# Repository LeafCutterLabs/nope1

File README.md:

# nope1
OP-1/LMN-3 interface based on the RP2040.<br>

Current QMK firmware is very basic (only midi keyboard implemented 53-76 and the LMN-3 CC signals, encoder are now working in vial! analog is not working)<br>
Joystick Analog pins: 26, 27<br>
Known Issues:<br>
	-Joystick switch trace is not connected<br>
 ToDo:<br>
 	-Get Vial running - DONE

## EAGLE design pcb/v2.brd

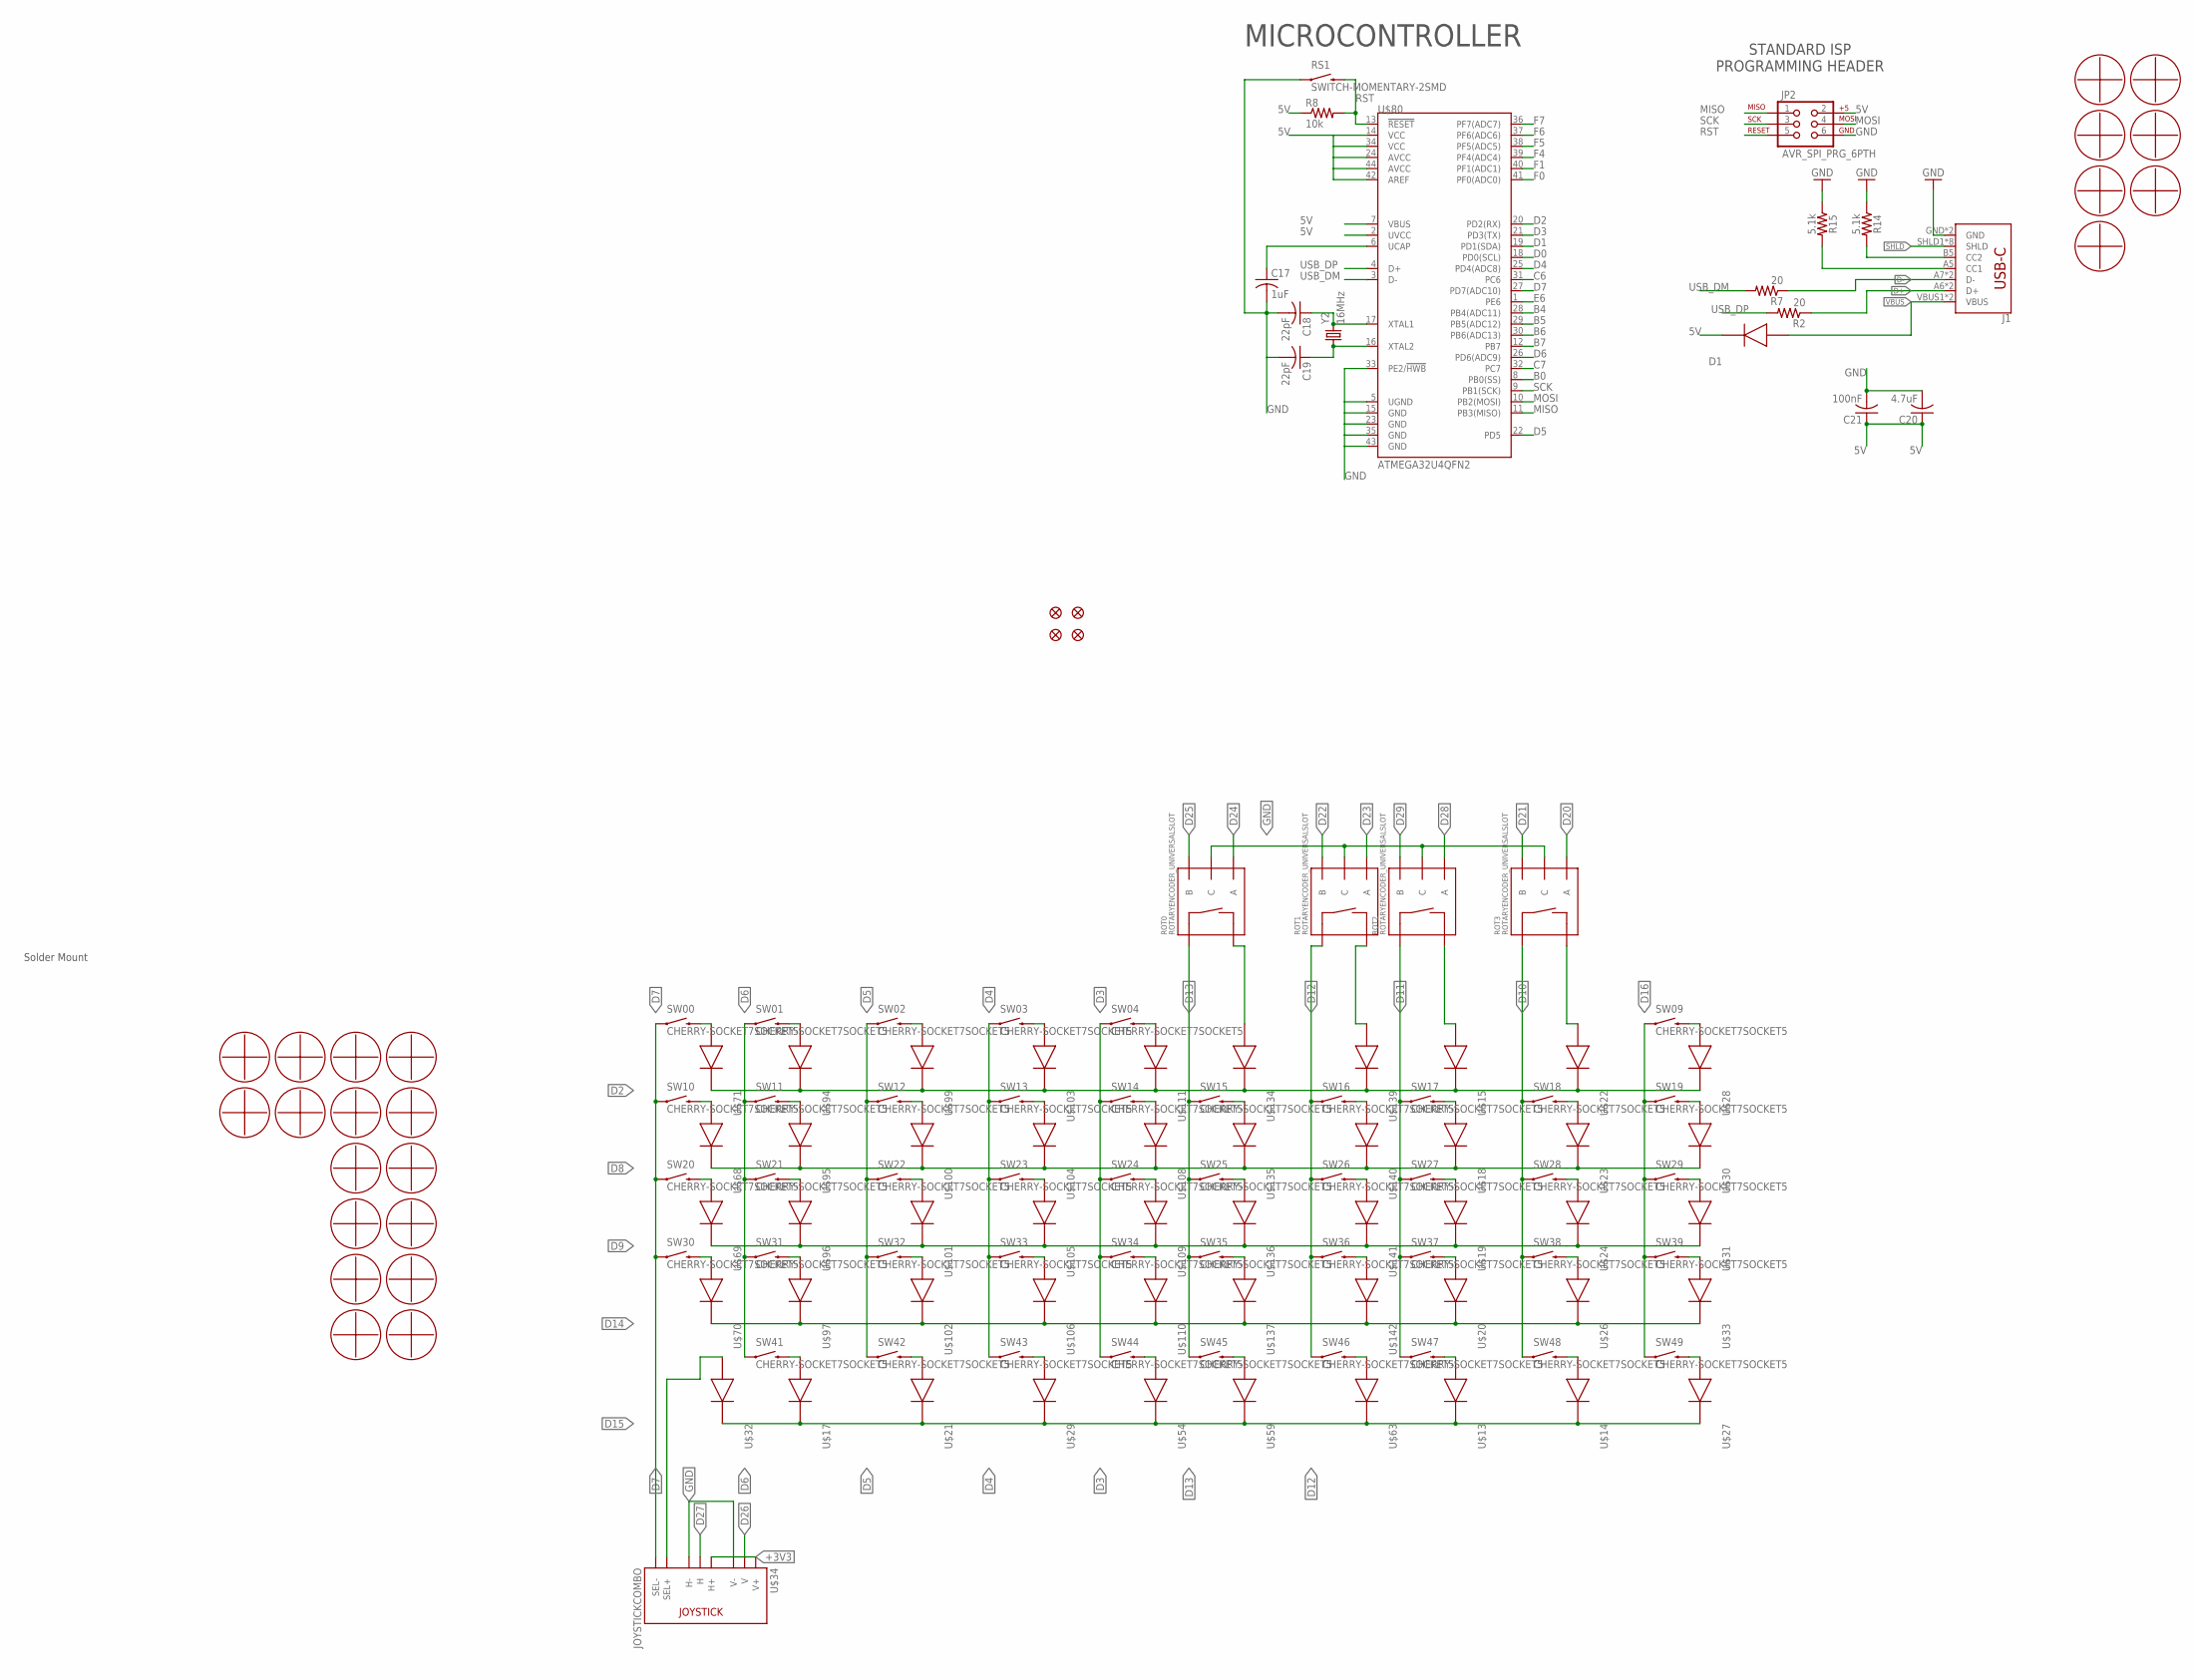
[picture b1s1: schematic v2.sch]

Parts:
C17: 1uF; C0603
C18, C19: 22pF; C0603
C20: 4.7uF; C0603
C21: 100nF; C0603
D1: SCHOTTKY; SOD-123
J1: USB_C16PIN; USB-C-16P
JP2: AVR_SPI_PRG_6PTH; 2X3
R2, R7: 20; R0603
R8: 10k; R0603
R14, R15: 5.1k; 0603
ROT0, ROT1, ROT2, ROT3: ROTARYENCODER_UNIVERSALSLOT; ROTARY_ENC_SLOT
RS1: SWITCH-MOMENTARY-2SMD; TACTILE_SWITCH_SMD
SW00, SW01, SW02, SW03, SW04, SW09, SW10, SW11, SW12, SW13, SW14, SW15, SW16, SW17, SW18, SW19, SW20, SW21, SW22, SW23, SW24, SW25, SW26, SW27, SW28, SW29, SW30, SW31, SW32, SW33, SW34, SW35, SW36, SW37, SW38, SW39, SW41, SW42, SW43, SW44, SW45, SW46, SW47, SW48, SW49: CHERRY-SOCKET7SOCKET5; CHERRY-SOCKET5
U$1, U$2, U$3, U$4, U$5, U$6, U$7, U$8, U$9, U$10, U$11, U$12, U$16, U$25, U$44, U$45: M2MOUNT
U$13, U$14, U$15, U$17, U$18, U$19, U$20, U$21, U$22, U$23, U$24, U$26, U$27, U$28, U$29, U$30, U$31, U$32, U$33, U$54, U$59, U$63, U$68, U$69, U$70, U$71, U$94, U$95, U$96, U$97, U$99, U$100, U$101, U$102, U$103, U$104, U$105, U$106, U$108, U$109, U$110, U$111, U$134, U$135, U$136, U$137, U$139, U$140, U$141, U$142: 1N4148WS; SOD-323SLIM
U$34: JOYSTICKCOMBO
U$35, U$36, U$37, U$40, U$41, U$42, U$43: M2MOUNT3.65HOLE; M2SOLDERC2916348
U$38, U$39, U$62, U$64: FIDUCIAL_1MM
U$80: ATMEGA32U4QFN2; QFN-44-NOPAD
Y2: 16MHz; RESONATOR3225

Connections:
5V: C20.1, C21.1, D1.CAT, JP2.2, R8.1, U$80.2 (UVCC), U$80.7 (VBUS), U$80.14 (VCC), U$80.24 (AVCC), U$80.34 (VCC), U$80.42 (AREF), U$80.44 (AVCC)
+3V3: U$34.H1 (H+), U$34.HS1 (H+), U$34.V1 (V+), U$34.VS1 (V+)
B0: U$80.8 (PB0(SS))
B4: U$80.28 (PB4(ADC11))
B5: U$80.29 (PB5(ADC12))
B6: U$80.30 (PB6(ADC13))
B7: U$80.12 (PB7)
C6: U$80.31 (PC6)
C7: U$80.32 (PC7)
CC3: J1.A5 (CC1), R15.2
CC4: J1.B5 (CC2), R14.2
D0: U$80.18 (PD0(SCL))
D1: U$80.19 (PD1(SDA))
D2: U$15.GND (CAT), U$22.GND (CAT), U$28.GND (CAT), U$71.GND (CAT), U$80.20 (PD2(RX)), U$94.GND (CAT), U$99.GND (CAT), U$103.GND (CAT), U$111.GND (CAT), U$134.GND (CAT), U$139.GND (CAT)
D3: SW04.A (1), SW14.A (1), SW24.A (1), SW34.A (1), SW44.A (1), U$80.21 (PD3(TX))
D4: SW03.A (1), SW13.A (1), SW23.A (1), SW33.A (1), SW43.A (1), U$80.25 (PD4(ADC8))
D5: SW02.A (1), SW12.A (1), SW22.A (1), SW32.A (1), SW42.A (1), U$80.22 (PD5)
D6: SW01.A (1), SW11.A (1), SW21.A (1), SW31.A (1), SW41.A (1), U$80.26 (PD6(ADC9))
D7: SW00.A (1), SW10.A (1), SW20.A (1), SW30.A (1), U$34.B1B (SEL-), U$34.B1B1 (SEL-), U$34.B2B (SEL-), U$34.B2B1 (SEL-), U$80.27 (PD7(ADC10))
D8: U$18.GND (CAT), U$23.GND (CAT), U$30.GND (CAT), U$68.GND (CAT), U$95.GND (CAT), U$100.GND (CAT), U$104.GND (CAT), U$108.GND (CAT), U$135.GND (CAT), U$140.GND (CAT)
D9: U$19.GND (CAT), U$24.GND (CAT), U$31.GND (CAT), U$69.GND (CAT), U$96.GND (CAT), U$101.GND (CAT), U$105.GND (CAT), U$109.GND (CAT), U$136.GND (CAT), U$141.GND (CAT)
D10: ROT3.SW+, SW18.A (1), SW28.A (1), SW38.A (1), SW48.A (1)
D11: ROT2.SW+, SW17.A (1), SW27.A (1), SW37.A (1), SW47.A (1)
D12: ROT1.SW+, SW16.A (1), SW26.A (1), SW36.A (1), SW46.A (1)
D13: ROT0.SW+, SW15.A (1), SW25.A (1), SW35.A (1), SW45.A (1)
D14: U$20.GND (CAT), U$26.GND (CAT), U$33.GND (CAT), U$70.GND (CAT), U$97.GND (CAT), U$102.GND (CAT), U$106.GND (CAT), U$110.GND (CAT), U$137.GND (CAT), U$142.GND (CAT)
D15: U$13.GND (CAT), U$14.GND (CAT), U$17.GND (CAT), U$21.GND (CAT), U$27.GND (CAT), U$29.GND (CAT), U$32.GND (CAT), U$54.GND (CAT), U$59.GND (CAT), U$63.GND (CAT)
D16: SW09.A (1), SW19.A (1), SW29.A (1), SW39.A (1), SW49.A (1)
D20: ROT3.A
D21: ROT3.B
D22: ROT1.B
D23: ROT1.A
D24: ROT0.A
D25: ROT0.B
D26: U$34.V2 (V), U$34.VS2 (V)
D27: U$34.H2 (H), U$34.HS2 (H)
D28: ROT2.A
D29: ROT2.B
D+: J1.A6 (D+), J1.B6 (D+), R2.1
D-: J1.A7 (D-), J1.B7 (D-), R7.1
E6: U$80.1 (PE6)
F0: U$80.41 (PF0(ADC0))
F1: U$80.40 (PF1(ADC1))
F4: U$80.39 (PF4(ADC4))
F5: U$80.38 (PF5(ADC5))
F6: U$80.37 (PF6(ADC6))
F7: U$80.36 (PF7(ADC7))
GND: C17.2, C18.2, C19.2, C20.2, C21.2, J1.GND, J1.GND2 (GND), JP2.6, R14.1, R15.1, ROT0.C, ROT1.C, ROT2.C, ROT3.C, RS1.1, U$34.H3 (H-), U$34.HS3 (H-), U$34.V3 (V-), U$34.VS3 (V-), U$80.5 (UGND), U$80.15 (GND), U$80.23 (GND), U$80.33 (PE2/!HWB), U$80.35 (GND), U$80.43 (GND)
MISO: JP2.1, U$80.11 (PB3(MISO))
MOSI: JP2.4, U$80.10 (PB2(MOSI))
unnamed: U$32.SIGNAL (ANO), U$34.B1A (SEL+), U$34.B1A1 (SEL+), U$34.B2A (SEL+), U$34.B2A1 (SEL+)
unnamed: SW47.B (2), U$13.SIGNAL (ANO)
unnamed: SW48.B (2), U$14.SIGNAL (ANO)
unnamed: ROT2.SW-, U$15.SIGNAL (ANO)
unnamed: SW17.B (2), U$18.SIGNAL (ANO)
unnamed: SW27.B (2), U$19.SIGNAL (ANO)
unnamed: SW37.B (2), U$20.SIGNAL (ANO)
unnamed: SW41.B (2), U$17.SIGNAL (ANO)
unnamed: ROT3.SW-, U$22.SIGNAL (ANO)
unnamed: SW18.B (2), U$23.SIGNAL (ANO)
unnamed: SW28.B (2), U$24.SIGNAL (ANO)
unnamed: SW38.B (2), U$26.SIGNAL (ANO)
unnamed: SW49.B (2), U$27.SIGNAL (ANO)
unnamed: SW09.B (2), U$28.SIGNAL (ANO)
unnamed: SW42.B (2), U$21.SIGNAL (ANO)
unnamed: SW19.B (2), U$30.SIGNAL (ANO)
unnamed: SW29.B (2), U$31.SIGNAL (ANO)
unnamed: SW39.B (2), U$33.SIGNAL (ANO)
unnamed: SW00.B (2), U$71.SIGNAL (ANO)
unnamed: SW43.B (2), U$29.SIGNAL (ANO)
unnamed: SW44.B (2), U$54.SIGNAL (ANO)
unnamed: C17.1, U$80.6 (UCAP)
unnamed: SW45.B (2), U$59.SIGNAL (ANO)
unnamed: SW10.B (2), U$68.SIGNAL (ANO)
unnamed: SW20.B (2), U$69.SIGNAL (ANO)
unnamed: SW30.B (2), U$70.SIGNAL (ANO)
unnamed: SW46.B (2), U$63.SIGNAL (ANO)
unnamed: SW01.B (2), U$94.SIGNAL (ANO)
unnamed: SW11.B (2), U$95.SIGNAL (ANO)
unnamed: SW21.B (2), U$96.SIGNAL (ANO)
unnamed: SW31.B (2), U$97.SIGNAL (ANO)
unnamed: SW02.B (2), U$99.SIGNAL (ANO)
unnamed: SW12.B (2), U$100.SIGNAL (ANO)
unnamed: SW22.B (2), U$101.SIGNAL (ANO)
unnamed: SW32.B (2), U$102.SIGNAL (ANO)
unnamed: SW14.B (2), U$108.SIGNAL (ANO)
unnamed: SW24.B (2), U$109.SIGNAL (ANO)
unnamed: SW34.B (2), U$110.SIGNAL (ANO)
unnamed: SW03.B (2), U$103.SIGNAL (ANO)
unnamed: SW13.B (2), U$104.SIGNAL (ANO)
unnamed: SW23.B (2), U$105.SIGNAL (ANO)
unnamed: SW33.B (2), U$106.SIGNAL (ANO)
unnamed: SW04.B (2), U$111.SIGNAL (ANO)
unnamed: ROT0.SW-, U$134.SIGNAL (ANO)
unnamed: SW15.B (2), U$135.SIGNAL (ANO)
unnamed: SW25.B (2), U$136.SIGNAL (ANO)
unnamed: SW35.B (2), U$137.SIGNAL (ANO)
unnamed: ROT1.SW-, U$139.SIGNAL (ANO)
unnamed: SW16.B (2), U$140.SIGNAL (ANO)
unnamed: SW26.B (2), U$141.SIGNAL (ANO)
unnamed: SW36.B (2), U$142.SIGNAL (ANO)
RST: JP2.5, R8.2, RS1.3 (2), U$80.13 (!RESET)
SCK: JP2.3, U$80.9 (PB1(SCK))
SHLD: J1.SHLD1 (SHLD), J1.SHLD2 (SHLD), J1.SHLD3 (SHLD), J1.SHLD4 (SHLD), J1.SHLD5 (SHLD), J1.SHLD6 (SHLD), J1.SHLD7 (SHLD), J1.SHLD8 (SHLD)
USB_DM: R7.2, U$80.3 (D-)
USB_DP: R2.2, U$80.4 (D+)
VBUS: D1.ANO, J1.VBUS1 (VBUS), J1.VBUS2 (VBUS)
XTAL1: C18.1, U$80.17 (XTAL1), Y2.P3 (2)
XTAL2: C19.1, U$80.16 (XTAL2), Y2.P1 (1)

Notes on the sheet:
Solder Mount
MICROCONTROLLER
STANDARD ISP PROGRAMMING HEADER

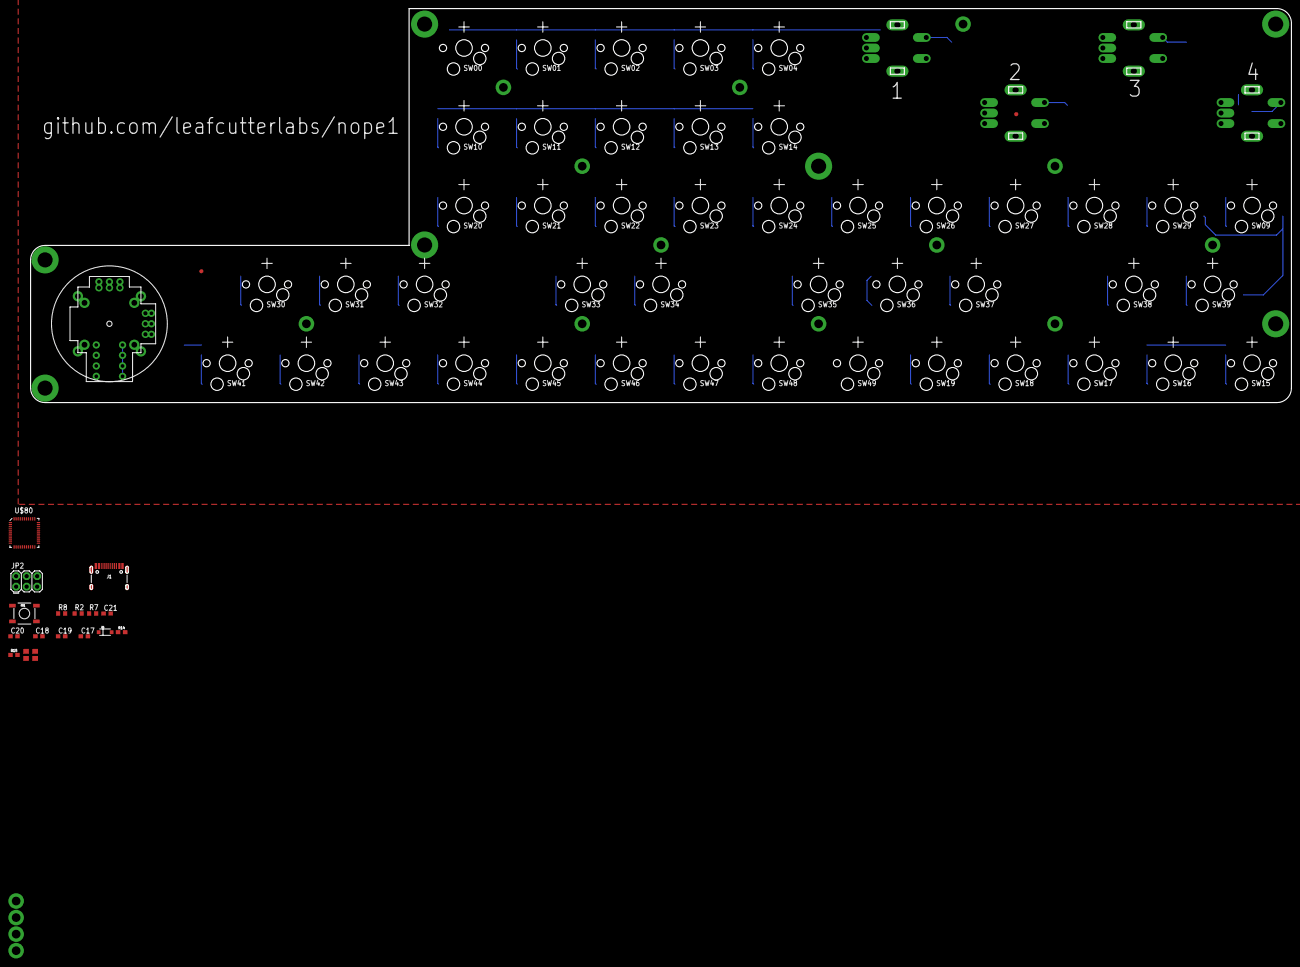
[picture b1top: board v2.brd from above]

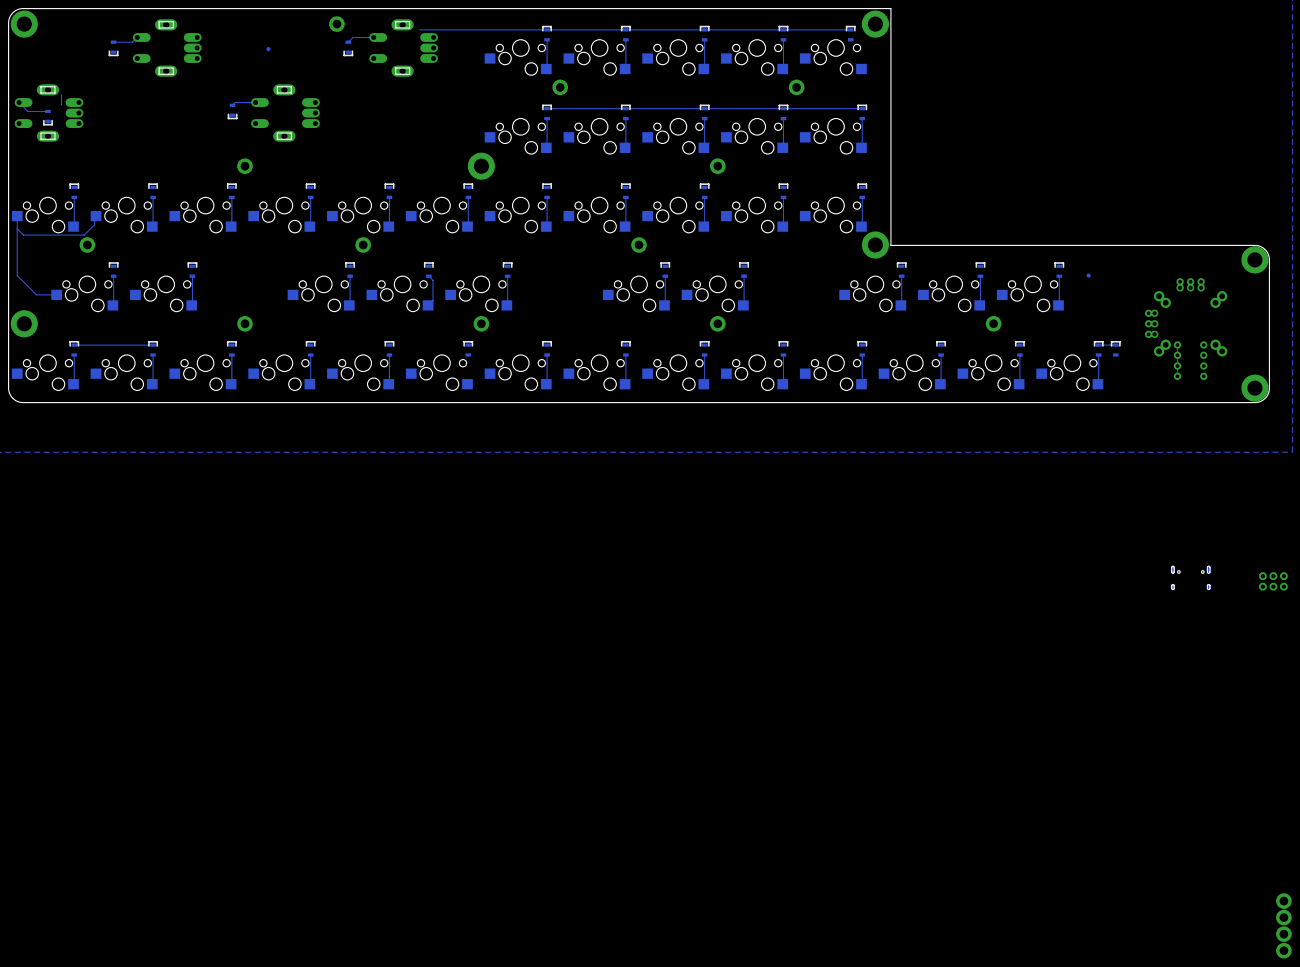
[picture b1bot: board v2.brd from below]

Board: 2 copper layers, 304.8 x 95.2 mm, 143 parts (59 on the bottom side), 85 nets.

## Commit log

2023-10-23 init
    first push
2023-10-24 update firmware
    add custom cc from lmn-3
2023-12-05 Updated VIAL firmware
    Full encoder support in VIAL

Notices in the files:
parts and their libraries:
microbuilder: This work is placed in the public domain, and may be freely used for commercial and non-commercial work with the following conditions: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
SparkFun-Connectors: Licensing: Creative Commons ShareAlike 4.0 International - https://creativecommons.org/licenses/by-sa/4.0
